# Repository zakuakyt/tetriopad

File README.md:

# tetriopad
my HackClub Blueprint submission - a custom macro pad for the online game tetr.io

## 1. schematic
this was my first time using kicad so I spent a bit more time on this but picked it up pretty quickly. I decided to add 2 RGB LEDs in addition to the keys - one that shines each time the spacebar is pressed, and one that just turns on when the board is plugged in.

## 2. routing
Using the hackpad tutorial, I routed all the components, using frontside and backside. I also added an image and some other random stuff to the silkscreen to make it cooler.

## 3. cad
I made a simple case for the board with some screw holes, a gap for the rp2040, and some nice beveled sides. I have some prior experience with fusion so this step was not too difficult.

## 4. BOM
BOM:

6x Cherry MX Switches

2x SK6812 MINI Leds

1x XIAO RP2040

6x Blank DSA Keycaps

3x M3x16 Bolt

3x M3 Heatset

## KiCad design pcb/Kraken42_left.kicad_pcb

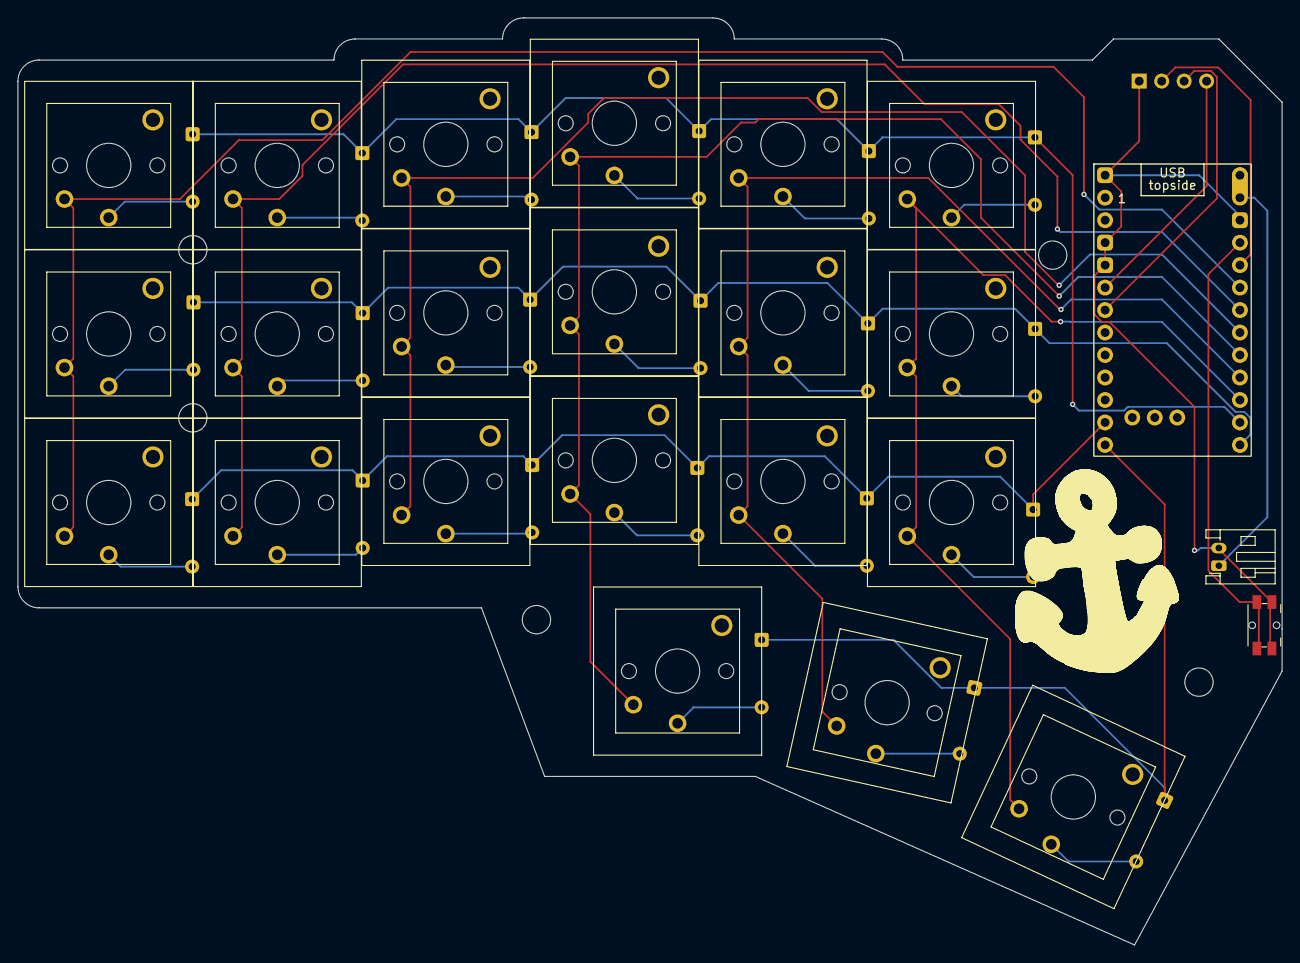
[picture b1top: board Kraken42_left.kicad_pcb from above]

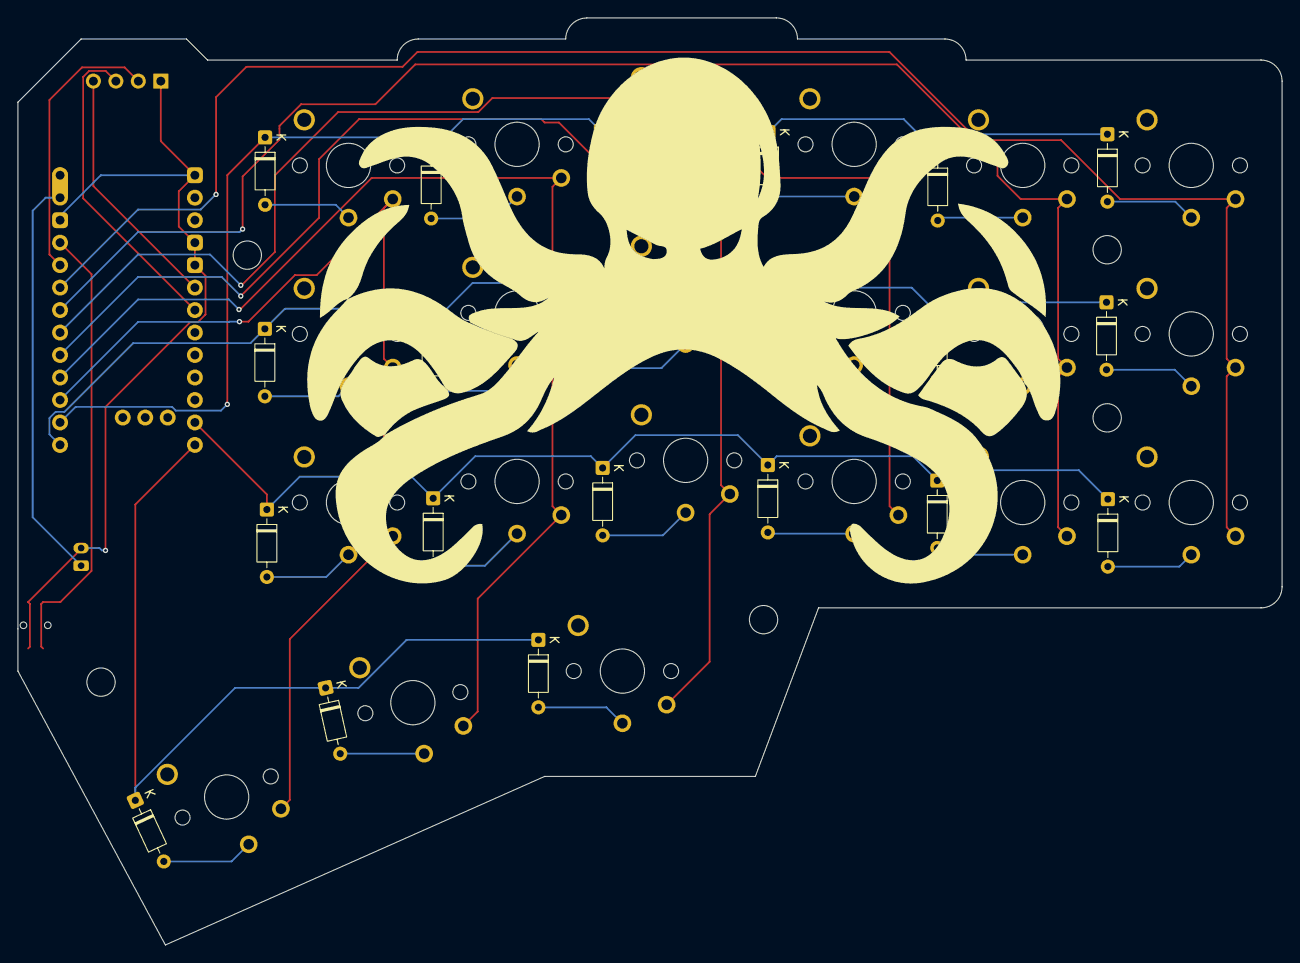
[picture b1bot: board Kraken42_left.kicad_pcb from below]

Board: 2 copper layers, 142.9 x 104.8 mm, 51 parts (21 on the bottom side), 37 nets.

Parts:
D1, D3, D5, D6, D9, D10, D13, D14, D15, D16, D17, D18, D25, D26, D27, D28, D29, D30, D37, D39, D41: D; D_DO-35_SOD27_P7.62mm_Horizontal
H1, H3, H4, H5, H6: MountingHole; MountingHole_3.2mm_M3
J1: OLED-128x32; OLED-128x32-cutout
J3: Conn_01x02_Socket; JST_PH_S2B-PH-K_1x02_P2.00mm_Horizontal
SW1, SW3, SW5, SW6, SW9, SW10, SW13, SW14, SW15, SW16, SW17, SW18, SW25, SW26, SW27, SW28, SW29, SW30, SW37, SW39, SW41: SW_Push; SW_choc_v1+v2_1u
SW45: SW_Push; Panasonic_EVQPUL_EVQPUC
U1: SuperMini nRF52840; SuperMini_nRF52840_AH_USBup

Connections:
COL0: SW1.1, SW13.1, SW25.1, U1.17 (P0.31-LF)
COL1: SW3.1, SW14.1, SW26.1, U1.18 (P0.29-LF)
COL2: SW5.1, SW15.1, SW27.1, U1.19 (P0.02-LF)
COL3: SW6.1, SW16.1, SW28.1, SW41.1, U1.20 (P1.15-LF)
COL4: SW9.1, SW17.1, SW29.1, SW39.1, U1.21 (P1.13-LF)
COL5: SW10.1, SW18.1, SW30.1, SW37.1, U1.22 (P1.11-LF)
GND: J1.1 (GND), J3.2, SW45.1, U1.3 (GND), U1.4 (GND), U1.14 (GND), U1.28 (GND)
unnamed: D1.2 (A), SW1.2
unnamed: D3.2 (A), SW3.2
unnamed: D5.2 (A), SW5.2
unnamed: D6.2 (A), SW6.2
unnamed: D9.2 (A), SW9.2
unnamed: D10.2 (A), SW10.2
unnamed: D13.2 (A), SW13.2
unnamed: D14.2 (A), SW14.2
unnamed: D15.2 (A), SW15.2
unnamed: D16.2 (A), SW16.2
unnamed: D17.2 (A), SW17.2
unnamed: D18.2 (A), SW18.2
unnamed: D25.2 (A), SW25.2
unnamed: D26.2 (A), SW26.2
unnamed: D27.2 (A), SW27.2
unnamed: D28.2 (A), SW28.2
unnamed: D29.2 (A), SW29.2
unnamed: D30.2 (A), SW30.2
unnamed: D37.2 (A), SW37.2
unnamed: D39.2 (A), SW39.2
unnamed: D41.2 (A), SW41.2
unnamed: J3.1, U1.13 (BAT+), U1.29 (BAT+)
RESET: SW45.2, U1.15 (RST)
ROW0: D1.1 (K), D3.1 (K), D5.1 (K), D6.1 (K), D9.1 (K), D10.1 (K), U1.23 (P0.10-LF)
ROW1: D13.1 (K), D14.1 (K), D15.1 (K), D16.1 (K), D17.1 (K), D18.1 (K), U1.24 (P0.09-LF)
ROW2: D25.1 (K), D26.1 (K), D27.1 (K), D28.1 (K), D29.1 (K), D30.1 (K), U1.11 (P1.04-LF)
ROW3: D37.1 (K), D39.1 (K), D41.1 (K), U1.12 (P1.06-LF)
SCK: J1.3 (SCL), U1.6 (P0.20)
SDA: J1.4 (SDA), U1.5 (P0.17)
VCC: J1.2 (VCC), U1.16 (3V3)

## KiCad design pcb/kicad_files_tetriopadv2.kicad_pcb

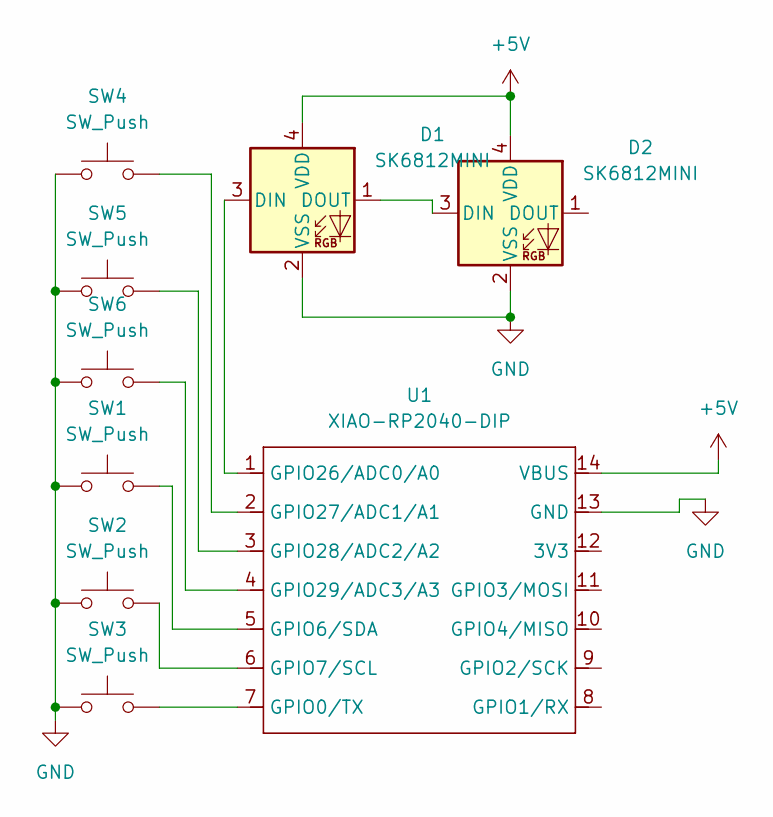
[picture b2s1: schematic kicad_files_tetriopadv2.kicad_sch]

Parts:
D1, D2: SK6812MINI; LED_SK6812MINI_PLCC4_3.5x3.5mm_P1.75mm
SW1, SW2, SW3, SW4, SW5, SW6: SW_Push; SW_Cherry_MX_1.00u_PCB
U1: XIAO-RP2040-DIP

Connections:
+5V: D1.4 (VDD), D2.4 (VDD), U1.14 (VBUS)
GND: D1.2 (VSS), D2.2 (VSS), SW1.1, SW2.1, SW3.1, SW4.1, SW5.1, SW6.1, U1.13 (GND)
unnamed: D1.3 (DIN), U1.1 (GPIO26/ADC0/A0)
unnamed: D1.1 (DOUT), D2.3 (DIN)
unnamed: SW3.2, U1.7 (GPIO0/TX)
unnamed: SW1.2, U1.5 (GPIO6/SDA)
unnamed: SW2.2, U1.6 (GPIO7/SCL)
unnamed: SW4.2, U1.2 (GPIO27/ADC1/A1)
unnamed: SW5.2, U1.3 (GPIO28/ADC2/A2)
unnamed: SW6.2, U1.4 (GPIO29/ADC3/A3)

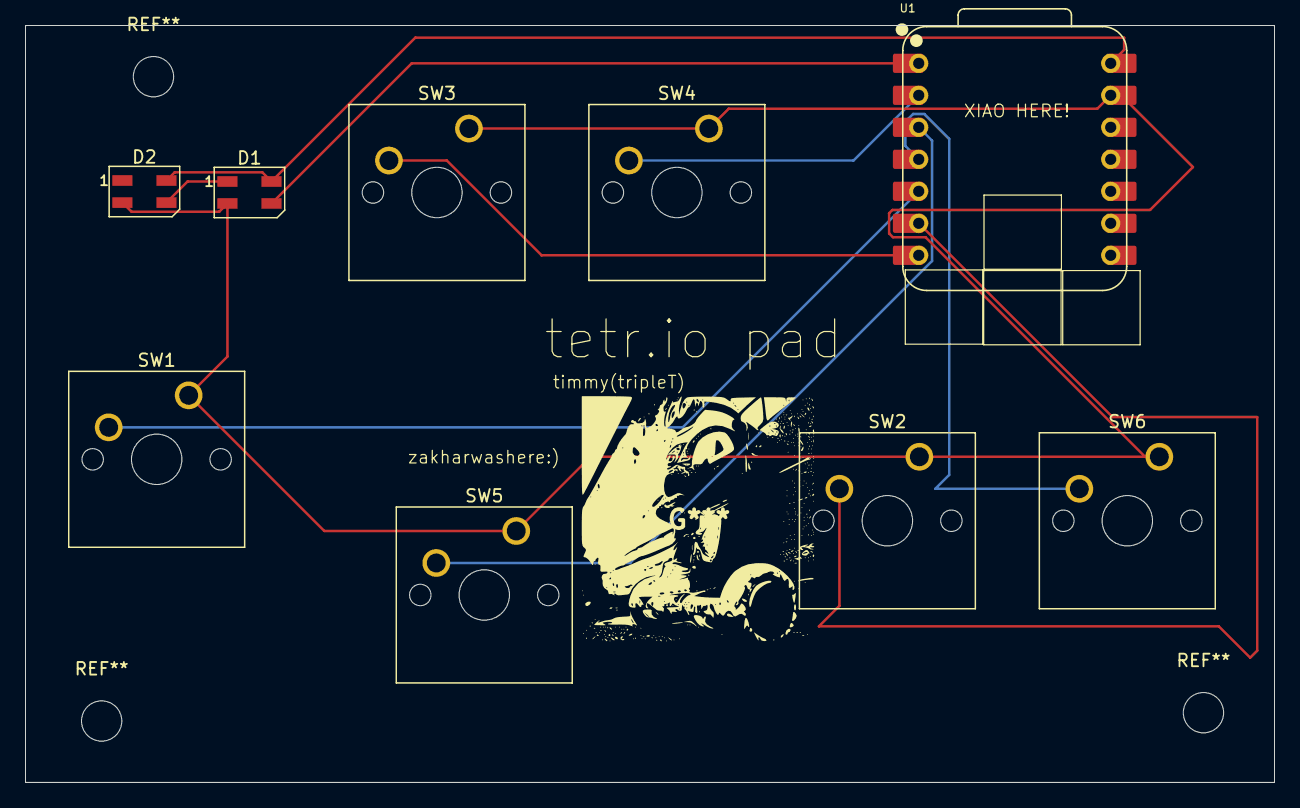
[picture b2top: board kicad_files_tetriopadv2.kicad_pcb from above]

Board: 2 copper layers, 99.2 x 60.1 mm, 9 parts (0 on the bottom side), 10 nets.

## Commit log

2025-11-26 Create temp
